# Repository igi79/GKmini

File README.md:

# GKmini
Geigercounter mini

based on https://sites.google.com/site/diygeigercounter/gk-mini

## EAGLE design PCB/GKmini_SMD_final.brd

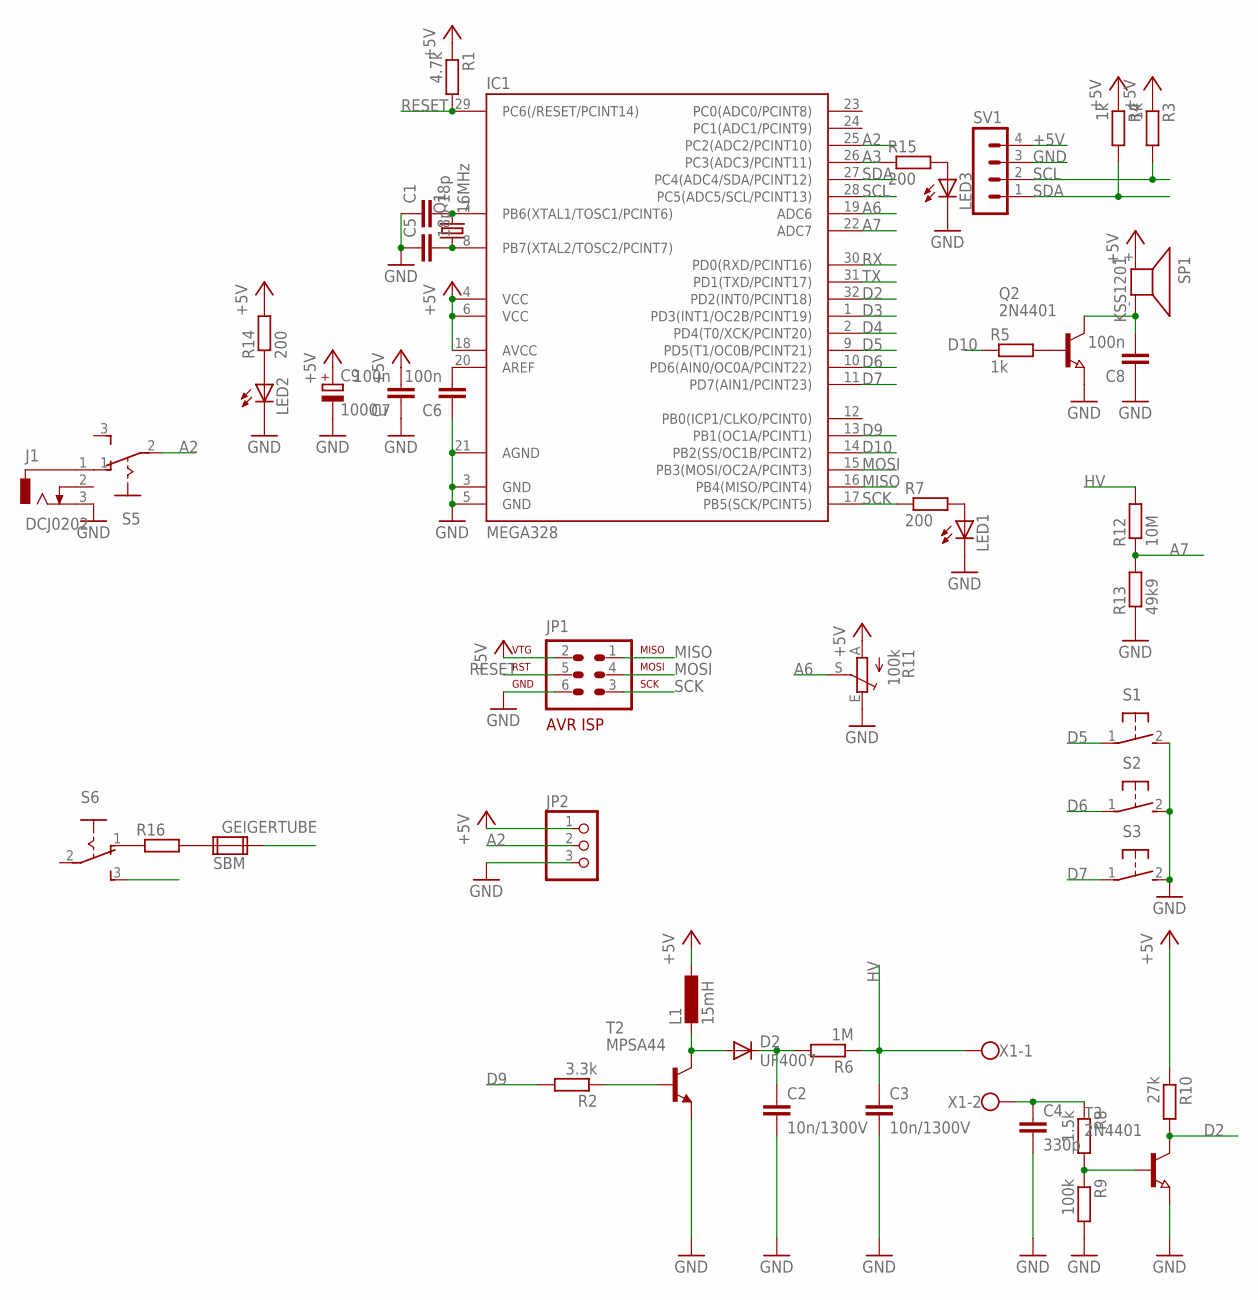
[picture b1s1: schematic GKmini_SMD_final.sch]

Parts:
C1, C5: 18p; C0805
C2, C3: 10n/1300V; C150-054X183
C4: 330p; C0805K
C6, C7, C8: 100n; C0805
C9: 1000u; 153CLV-1012
D2: UF4007; C1702-05
GEIGERTUBE: SBM
IC1: MEGA328; TQFP32-08
J1: DCJ0202
JP1: AVR-ISP-6R
JP2: PINHD-1X3; 1X03
L1: 15mH; 6000-XXXX-RC
LED1, LED2, LED3: LED3MM
Q1: 16MHz; HC49UP
Q2: 2N4401; SOT23W
R1: 4.7k; R0805
R2: 3.3k; R0805
R3, R4, R5: 1k; R0805
R6: 1M; 0207/5V
R7, R14, R15: 200; R0805
R8: 1.5k; R0805W
R9: 100k; R0805W
R10: 27k; R0805W
R11: 100k; S64Y
R12: 10M; R0805
R13: 49k9; R0805
R16: R-EU_R1206W; R1206W
S1, S2, S3: 31-XX; B3F-31XX
S5, S6: 255SB
SP1: KSS1201
SV1: MA04-1
T2: MPSA44; TO92-EBC-OVAL
T3: 2N4401; SOT23W
X1: W237-102

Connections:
+5V: C7.2, C9.+, IC1.4 (VCC), IC1.6 (VCC), IC1.18 (AVCC), JP1.2, JP2.1, L1.1, R1.1, R3.1, R4.1, R10.1, R11.A, R14.2, SP1.+ (1), SV1.4
A2: IC1.25 (PC2(ADC2/PCINT10)), JP2.2, S5.2
A3: IC1.26 (PC3(ADC3/PCINT11)), R15.1
A6: IC1.19 (ADC6), R11.S
A7: IC1.22 (ADC7), R12.1, R13.2
D2: IC1.32 (PD2(INT0/PCINT18)), R10.2, T3.2 (C)
D3: IC1.1 (PD3(INT1/OC2B/PCINT19))
D4: IC1.2 (PD4(T0/XCK/PCINT20))
D5: IC1.9 (PD5(T1/OC0B/PCINT21)), S1.1
D6: IC1.10 (PD6(AIN0/OC0A/PCINT22)), S2.1
D7: IC1.11 (PD7(AIN1/PCINT23)), S3.1
D9: IC1.13 (PB1(OC1A/PCINT1)), R2.2
D10: IC1.14 (PB2(SS/OC1B/PCINT2)), R5.1
GND: C1.1, C2.2, C3.2, C4.2, C5.1, C6.1, C7.1, C8.1, C9.-, IC1.3 (GND), IC1.5 (GND), IC1.21 (AGND), J1.3, JP1.6, JP2.3, LED1.K (C), LED2.K (C), LED3.K (C), Q2.3 (E), R9.2, R11.E, R13.1, S1.2 (S), S2.2 (S), S3.2 (S), SV1.3, T2.E, T3.3 (E)
HV: C3.1, R6.1, R12.2, X1.1
MISO: IC1.16 (PB4(MISO/PCINT4)), JP1.1
MOSI: IC1.15 (PB3(MOSI/OC2A/PCINT3)), JP1.4
unnamed: C1.2, IC1.7 (PB6(XTAL1/TOSC1/PCINT6)), Q1.2
unnamed: C5.2, IC1.8 (PB7(XTAL2/TOSC2/PCINT7)), Q1.1
unnamed: C6.2, IC1.20 (AREF)
unnamed: Q2.1 (B), R5.2
unnamed: C8.2, Q2.2 (C), SP1.- (2)
unnamed: LED1.A, R7.2
unnamed: D2.A, L1.2, T2.C
unnamed: C2.1, D2.C, R6.2
unnamed: LED2.A, R14.1
unnamed: R2.1, T2.B
unnamed: C4.1, R8.1, X1.2
unnamed: R8.2, R9.1, T3.1 (B)
unnamed: R16.1, S6.1 (O)
unnamed: LED3.A, R15.2
unnamed: J1.1, S5.1 (O)
unnamed: GEIGERTUBE.1A, R16.2
RESET: IC1.29 (PC6(/RESET/PCINT14)), JP1.5, R1.2
RX: IC1.30 (PD0(RXD/PCINT16))
SCK: IC1.17 (PB5(SCK/PCINT5)), JP1.3, R7.1
SCL: IC1.28 (PC5(ADC5/SCL/PCINT13)), R3.2, SV1.2
SDA: IC1.27 (PC4(ADC4/SDA/PCINT12)), R4.2, SV1.1
TX: IC1.31 (PD1(TXD/PCINT17))

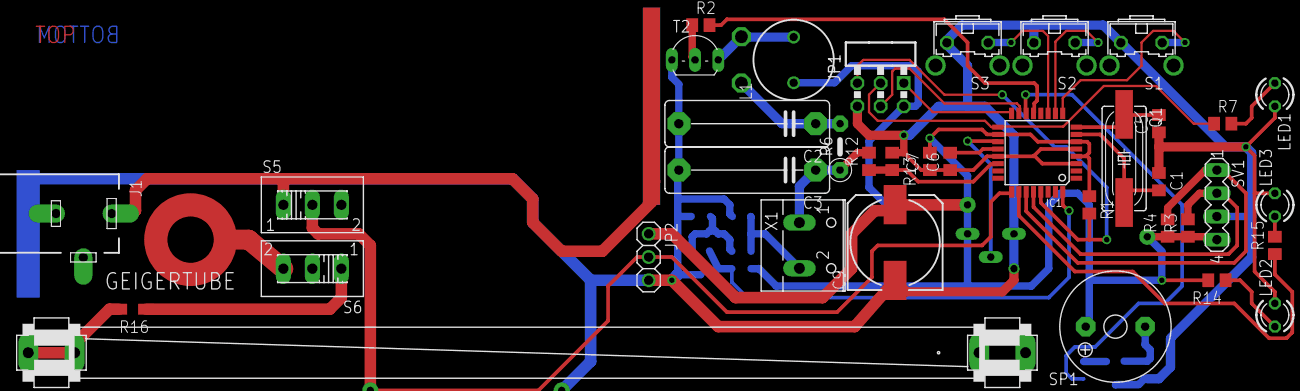
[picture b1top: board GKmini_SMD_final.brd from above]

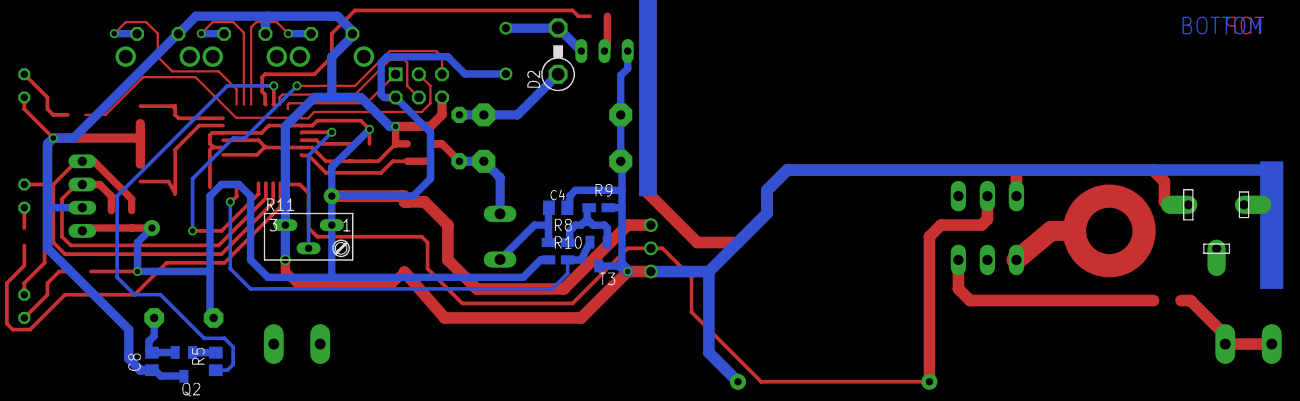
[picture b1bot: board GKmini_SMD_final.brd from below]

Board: 2 copper layers, 47 parts (10 on the bottom side), 35 nets.

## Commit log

2016-03-12 GK final
2016-03-20 PCB in PDF
